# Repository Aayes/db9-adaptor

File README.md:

#### 介绍
由于经常用到CAN总线设备，每次都要接线很不方便，特意设计了一个DB9转接头，把DB9转成接线端子，还带有终端电阻拨码和测试钩。

下面是做出来的实物：

#### 开发环境

KiCad 5.1.4

#### 购买成品

如果您想直接购买成品，请点击此处：[DB9转接头](https://item.taobao.com/item.htm?spm=a230r.1.14.30.3dc67ebcwtaL58&id=662251479579&ns=1&abbucket=12#detail)

#### 参与贡献

1. 如果有任何建议、帮助请联系QQ：3167139165
2. 汽车电子交流QQ群：678397352

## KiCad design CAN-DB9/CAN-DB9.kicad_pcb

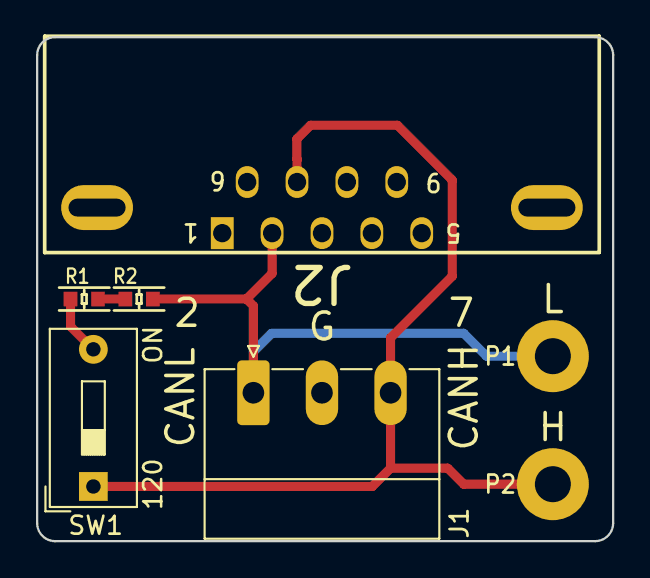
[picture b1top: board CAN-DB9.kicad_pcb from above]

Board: 2 copper layers, 32.0 x 28.0 mm, 7 parts (0 on the bottom side), 5 nets.

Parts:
J1: Conn_01x03; PhoenixContact_MC_1,5_3-G-3.81_1x03_P3.81mm_Horizontal
J2: DB9_Female_MountingHoles; DB9P-MR_DMR-9S-1
P1, P2: P; HOLE2-4
R1, R2: 13199827,62Ω,1%,0603-Car; SR0603
SW1: SW_DIP_x01; SW_DIP_SPSTx01_Slide_9.78x4.72mm_W7.62mm_P2.54mm

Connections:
CANH: J1.3, J2.7, P2.1, SW1.1
CANL: J1.1, J2.2, P1.1, R2.2
GND: J1.2, J2.3
unnamed: R1.1, SW1.2
unnamed: R1.2, R2.1
